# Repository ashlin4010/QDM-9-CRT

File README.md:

# QDM-9-CRT NANO Driver #

This repository contains the PCB and software to build a simple TTL video driver using an Arduino Nano.

It also has a Gamepad plug. 

## Building ##
 1. [Install AVR 8-Bit Toolchain](https://www.microchip.com/en-us/tools-resources/develop/microchip-studio/gcc-compilers)
 2. make && make upload 

## PCB BOM ##

| Quantity | Part | Link |
|:---:|:---:|:---:|
| 1 | 1K Resistor |  |
| 1 | Barrel Jack | https://www.digikey.co.nz/en/products/detail/same-sky-formerly-cui-devices/PJ-037A/1644545 |
| 1 | 74LS165N |  |
| 1 | POT | https://www.digikey.co.nz/en/products/detail/amphenol-piher-sensing-systems/PT10LV10-222A2020-PM-S/9555921 |
| 1 | Screw Terminal 6 POS | https://www.aliexpress.com/item/1005001677869988.html? |
| 1 | LM7805 | https://www.digikey.co.nz/en/products/detail/stmicroelectronics/L7805ABV/634711 |
| 1 | 0.1uF |  |
| 1 | 0.22uF |  |
| 1 | 3mm LED RED |  |
| 1 | Nano |  |
| 1 | DB-9 Female | https://www.digikey.co.nz/en/products/detail/assmann-wsw-components/A-DS-09-A-KG-T2S/1241804 |
| 1 | Game Pad |  https://www.aliexpress.com/item/1005005697321299.html |

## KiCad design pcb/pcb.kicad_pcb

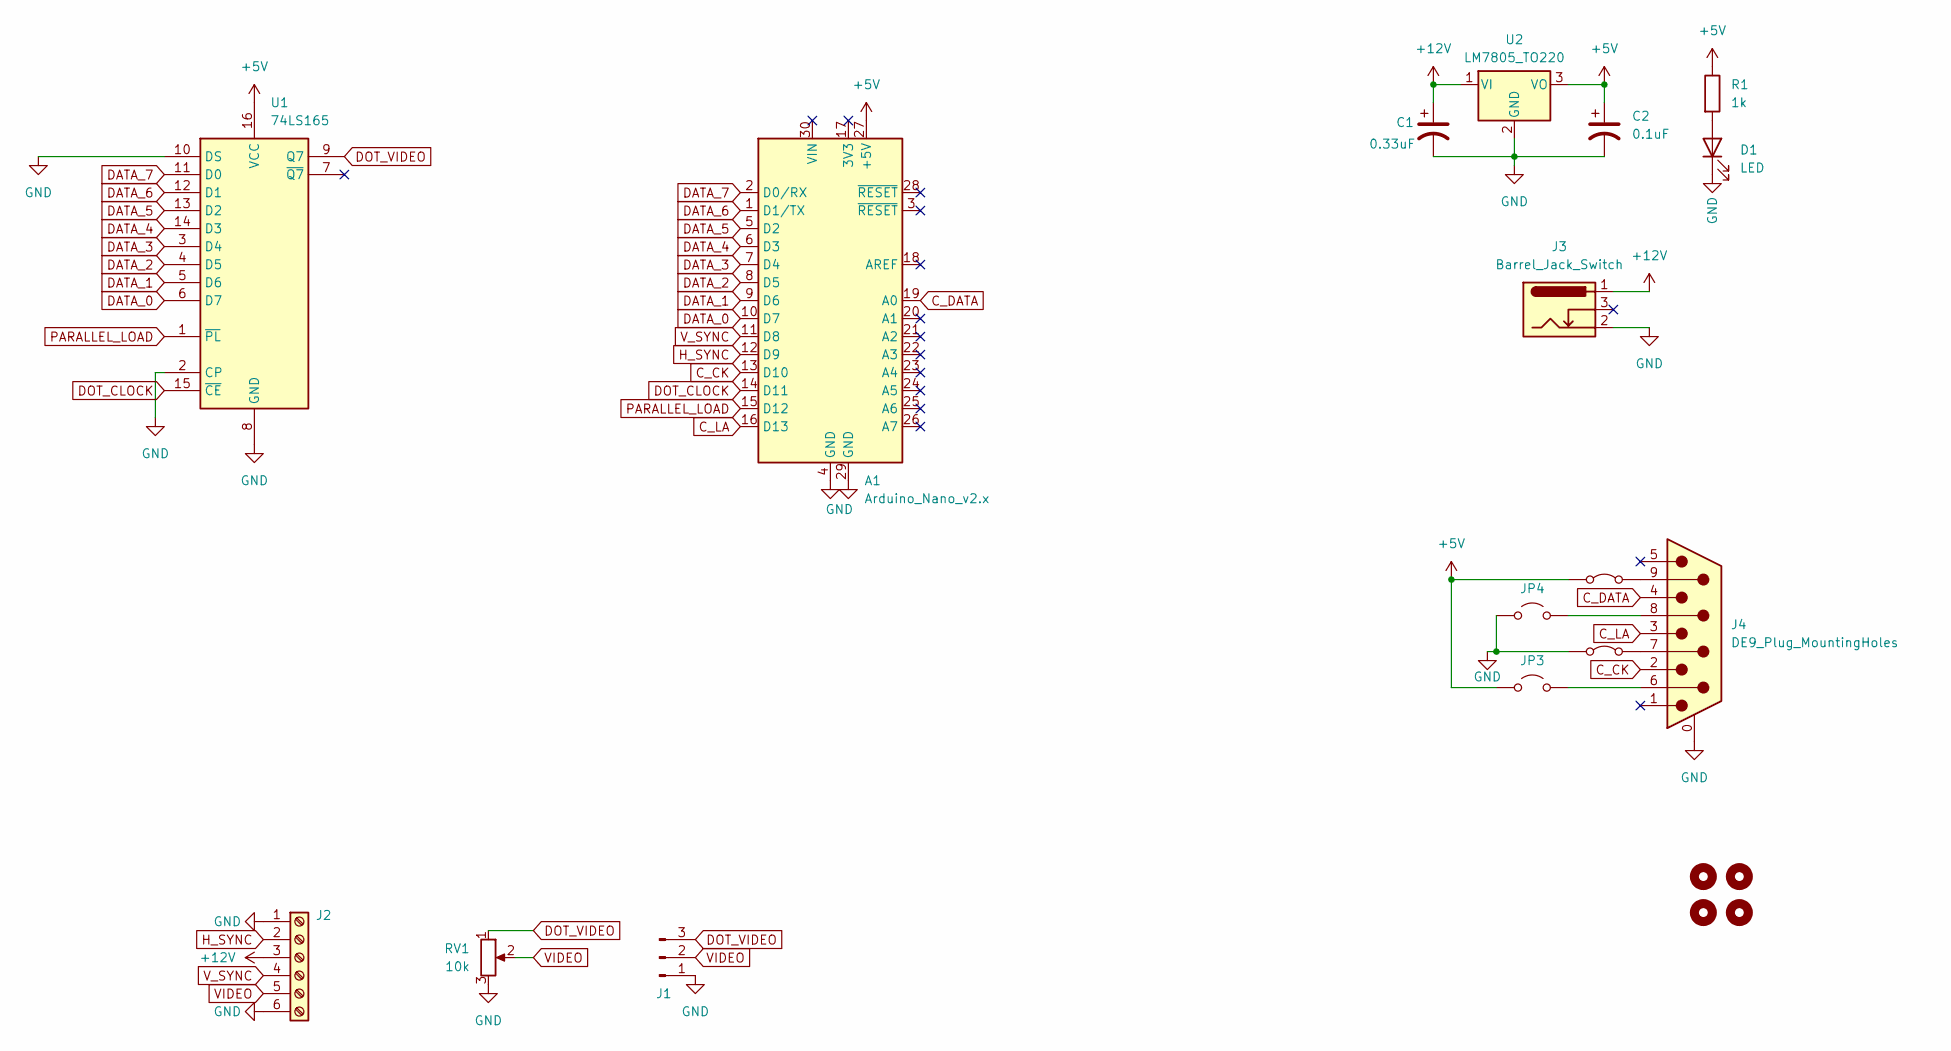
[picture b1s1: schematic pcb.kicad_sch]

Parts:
A1: Arduino_Nano_v2.x; Arduino_Nano
C1: 0.33uF; CP_Radial_D5.0mm_P2.00mm
C2: 0.1uF; CP_Radial_D4.0mm_P1.50mm
D1: LED; LED_D3.0mm
H1, H2, H3, H4: MountingHole; MountingHole_3.2mm_M3
J1: Conn_01x03_Pin; PinSocket_1x03_P2.54mm_Vertical
J2: Screw_Terminal_01x06; TerminalBlock_Xinya_XY308-2.54-6P_1x06_P2.54mm_Horizontal
J3: Barrel_Jack_Switch; BarrelJack_GCT_DCJ200-10-A_Horizontal
J4: DE9_Plug_MountingHoles; DSUB-9_Female_Horizontal_P2.77x2.84mm_EdgePinOffset7.70mm_H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
JP1, JP2: Jumper_2_Bridged; SolderJumper-2_P1.3mm_Bridged_RoundedPad1.0x1.5mm
JP3, JP4: Jumper_2_Open; SolderJumper-2_P1.3mm_Open_RoundedPad1.0x1.5mm
R1: 1k; R_Axial_DIN0204_L3.6mm_D1.6mm_P7.62mm_Horizontal
RV1: 10k; Potentiometer_Piher_PT-10-V10_Vertical
U1: 74LS165; DIP-16_W7.62mm_Socket
U2: LM7805_TO220; TO-220-3_Vertical

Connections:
+5V: A1.27 (+5V), C2.1, JP1.1 (A), JP3.1 (A), R1.1, U1.16 (VCC), U2.3 (VO)
+12V: C1.1, J2.3, J3.1, U2.1 (VI)
C_CK: A1.13 (D10), J4.2
C_DATA: A1.19 (A0), J4.4
C_LA: A1.16 (D13), J4.3
DATA_0: A1.10 (D7), U1.6 (D7)
DATA_1: A1.9 (D6), U1.5 (D6)
DATA_2: A1.8 (D5), U1.4 (D5)
DATA_3: A1.7 (D4), U1.3 (D4)
DATA_4: A1.6 (D3), U1.14 (D3)
DATA_5: A1.5 (D2), U1.13 (D2)
DATA_6: A1.1 (D1/TX), U1.12 (D1)
DATA_7: A1.2 (D0/RX), U1.11 (D0)
DOT_CLOCK: A1.14 (D11), U1.15 (~CE)
DOT_VIDEO: J1.3, RV1.1, U1.9 (Q7)
GND: A1.4 (GND), A1.29 (GND), C1.2, C2.2, D1.1 (K), J1.1, J2.1, J2.6, J3.2, J4.0 (PAD), JP2.1 (A), JP4.1 (A), RV1.3, U1.2 (CP), U1.8 (GND), U1.10 (DS), U2.2 (GND)
H_SYNC: A1.12 (D9), J2.2
unnamed: D1.2 (A), R1.2
unnamed: J4.9, JP1.2 (B)
unnamed: J4.7, JP2.2 (B)
unnamed: J4.6, JP3.2 (B)
unnamed: J4.8, JP4.2 (B)
PARALLEL_LOAD: A1.15 (D12), U1.1 (~PL)
VIDEO: J1.2, J2.5, RV1.2
V_SYNC: A1.11 (D8), J2.4

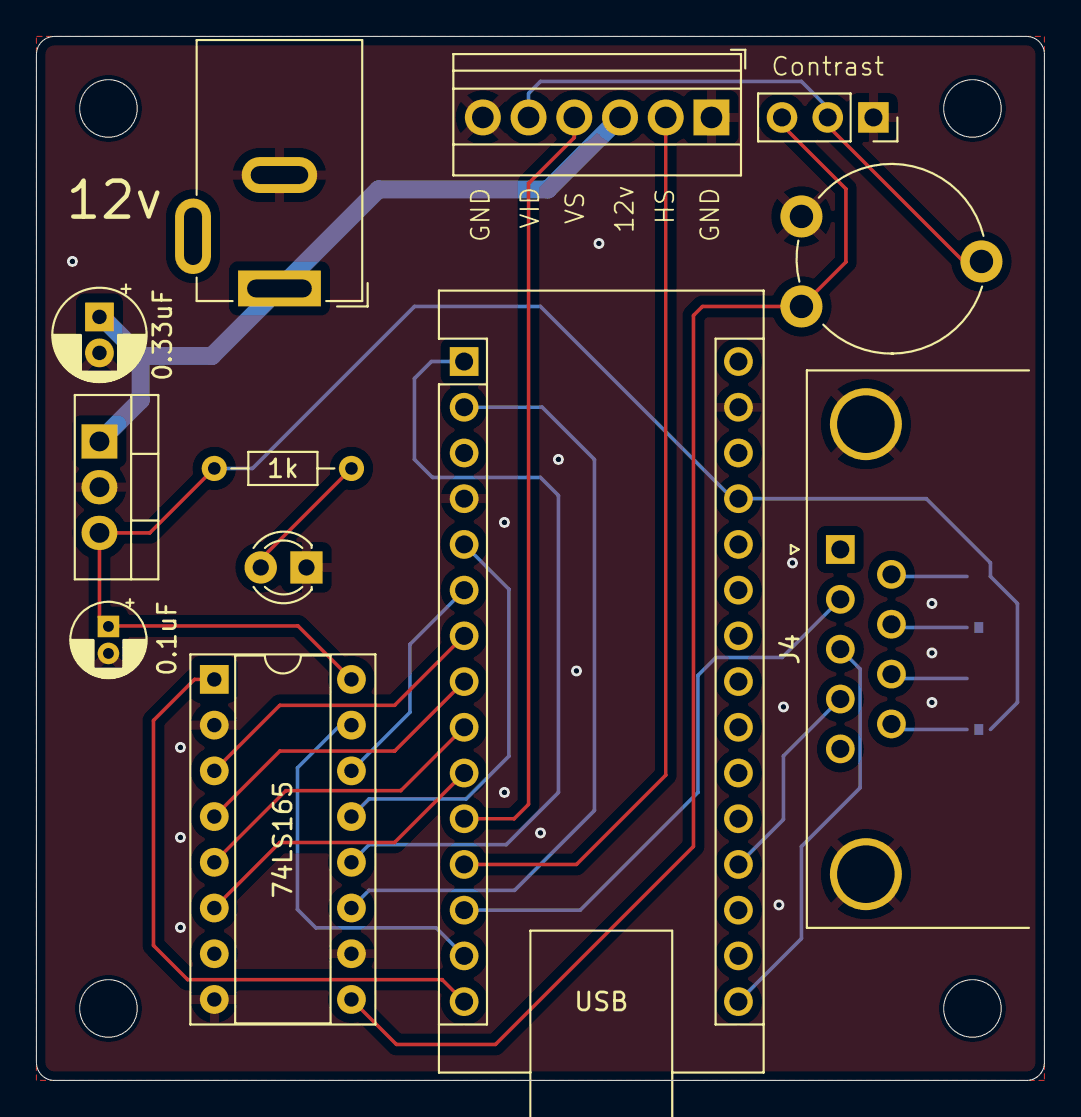
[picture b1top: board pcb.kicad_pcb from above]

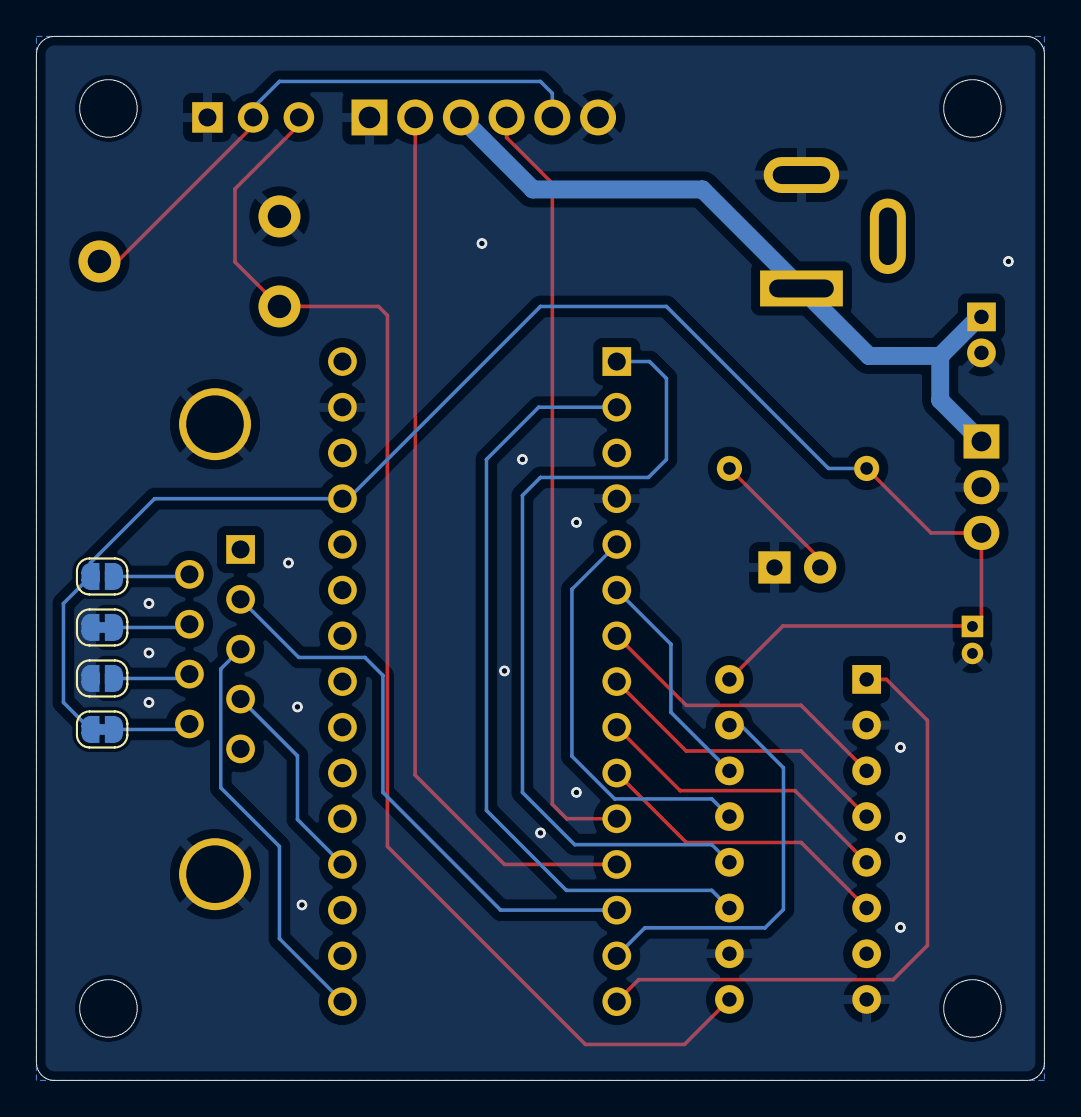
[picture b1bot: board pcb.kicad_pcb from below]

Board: 2 copper layers, 56.0 x 58.0 mm, 20 parts (4 on the bottom side), 25 nets.

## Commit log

2024-08-17 Simple scrip to draw text graphics to the display
2024-08-17 Increased max TEXT_COLUMNS to 25
2024-08-17 Lost 2 columns but gained 8000+ cycles per frame for game logic
2024-08-17 There is some jitter I will try rewrite it
2024-08-31 Moved the project to AVR
2024-09-01 Trying out some asm
2024-09-21 Added PCB
2024-12-06 New PDB files
2024-12-07 Update AVR code
2024-12-07 Added make file
2024-12-07 Added .vscode settings for AVR
2024-12-07 Fix backwards data lines
